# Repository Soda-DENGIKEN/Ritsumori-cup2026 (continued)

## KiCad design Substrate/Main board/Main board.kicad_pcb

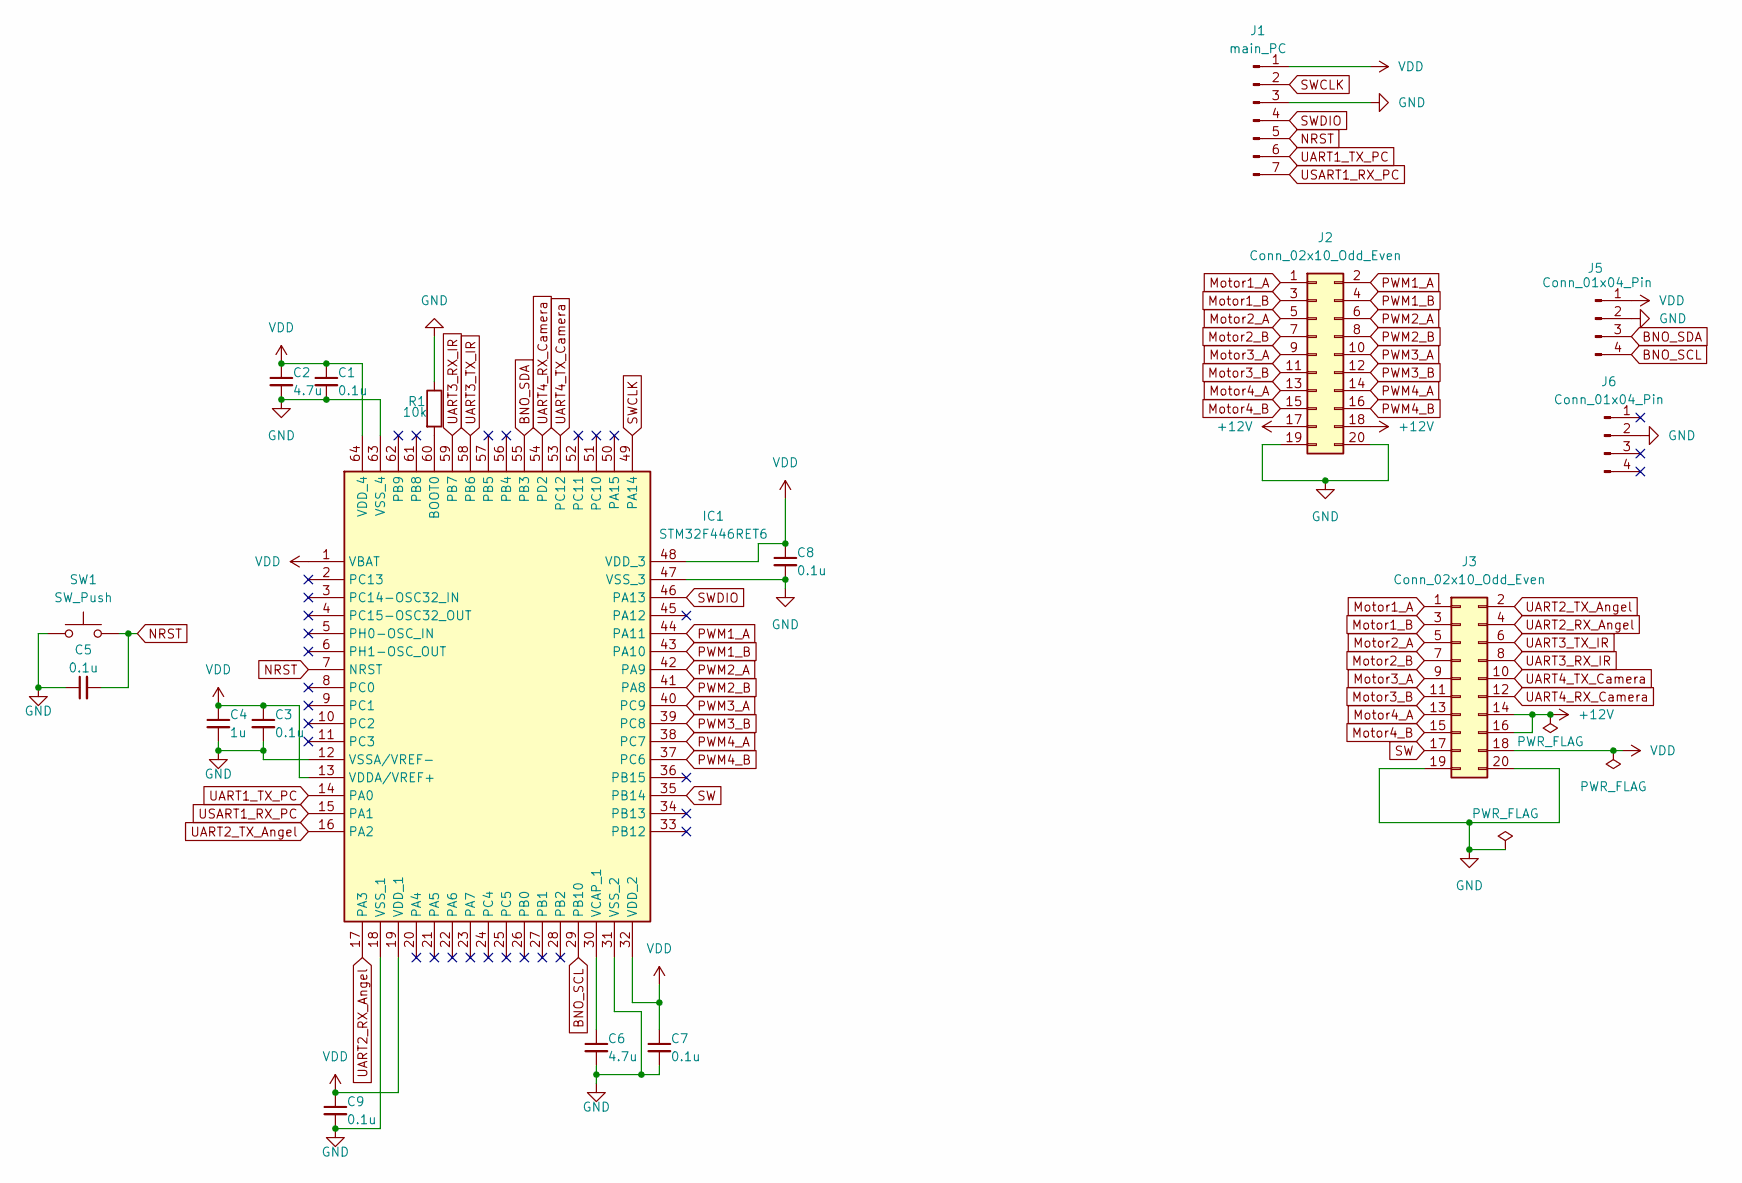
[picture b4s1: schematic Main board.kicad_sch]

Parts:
C1, C3, C5, C7, C8, C9: 0.1u; C_0603_1608Metric
C2, C6: 4.7u; C_0603_1608Metric
C4: 1u; C_0603_1608Metric
IC1: STM32F446RET6; LQFP-64_10x10mm_P0.5mm; Manufacturer_Part_Number STM32F446RET6; Mouser Part Number 511-STM32F446RET6
J1: main_PC; PinHeader_1x07_P2.54mm_Vertical
J2: Conn_02x10_Odd_Even; PinHeader_2x10_P2.54mm_Vertical
J3: Conn_02x10_Odd_Even; IDC-Header_2x10_P2.54mm_Vertical
J5, J6: Conn_01x04_Pin; PinSocket_1x04_P2.54mm_Vertical
R1: 10k; R_0603_1608Metric
SW1: SW_Push; SKRPABE010

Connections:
+12V: J2.17, J2.18, J3.14, J3.16
BNO_SCL: IC1.29 (PB10), J5.4
BNO_SDA: IC1.55 (PB3), J5.3
GND: C1.2, C2.2, C3.2, C4.2, C5.1, C6.2, C7.2, C8.2, C9.2, IC1.12 (VSSA/VREF-), IC1.18 (VSS_1), IC1.31 (VSS_2), IC1.47 (VSS_3), IC1.63 (VSS_4), J1.3, J2.19, J2.20, J3.19, J3.20, J5.2, J6.2, R1.1, SW1.1
Motor1_A: J2.1, J3.1
Motor1_B: J2.3, J3.3
Motor2_A: J2.5, J3.5
Motor2_B: J2.7, J3.7
Motor3_A: J2.9, J3.9
Motor3_B: J2.11, J3.11
Motor4_A: J2.13, J3.13
Motor4_B: J2.15, J3.15
NRST: C5.2, IC1.7 (NRST), J1.5, SW1.2
unnamed: IC1.60 (BOOT0), R1.2
unnamed: C6.1, IC1.30 (VCAP_1)
PWM1_A: IC1.44 (PA11), J2.2
PWM1_B: IC1.43 (PA10), J2.4
PWM2_A: IC1.42 (PA9), J2.6
PWM2_B: IC1.41 (PA8), J2.8
PWM3_A: IC1.40 (PC9), J2.10
PWM3_B: IC1.39 (PC8), J2.12
PWM4_A: IC1.38 (PC7), J2.14
PWM4_B: IC1.37 (PC6), J2.16
SW: IC1.35 (PB14), J3.17
SWCLK: IC1.49 (PA14), J1.2
SWDIO: IC1.46 (PA13), J1.4
UART1_TX_PC: IC1.14 (PA0), J1.6
UART2_RX_Angel: IC1.17 (PA3), J3.4
UART2_TX_Angel: IC1.16 (PA2), J3.2
UART3_RX_IR: IC1.59 (PB7), J3.8
UART3_TX_IR: IC1.58 (PB6), J3.6
UART4_RX_Camera: IC1.54 (PD2), J3.12
UART4_TX_Camera: IC1.53 (PC12), J3.10
USART1_RX_PC: IC1.15 (PA1), J1.7
VDD: C1.1, C2.1, C3.1, C4.1, C7.1, C8.1, C9.1, IC1.1 (VBAT), IC1.13 (VDDA/VREF+), IC1.19 (VDD_1), IC1.32 (VDD_2), IC1.48 (VDD_3), IC1.64 (VDD_4), J1.1, J3.18, J5.1

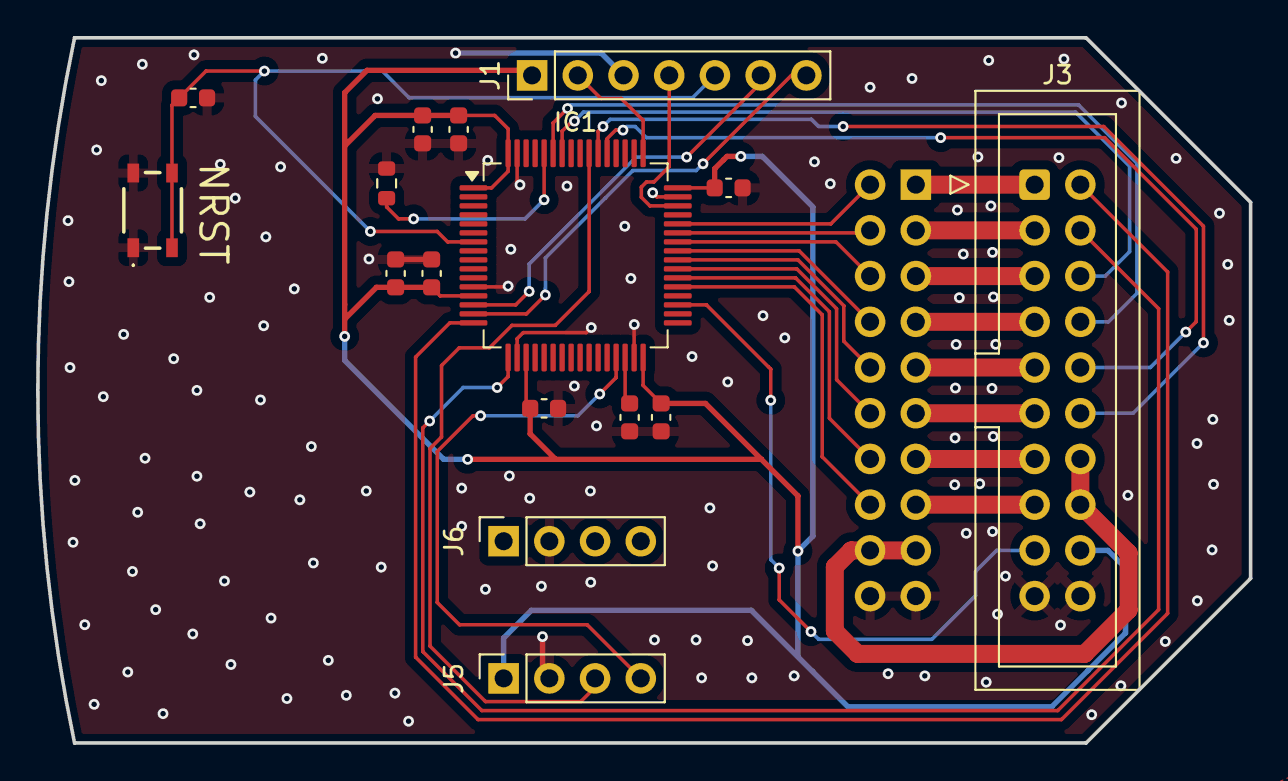
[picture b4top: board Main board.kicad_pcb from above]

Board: 2 copper layers, 67.4 x 39.2 mm, 17 parts (1 on the bottom side), 35 nets.

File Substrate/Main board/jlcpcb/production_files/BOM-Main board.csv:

Comment,Designator,Footprint,LCSC,Quantity
0.1u,"C1,C3,C5,C7,C8,C9",C_0603_1608Metric,C14663,6
10k,R1,R_0603_1608Metric,C25804,1
1u,C4,C_0603_1608Metric,C15849,1
4.7u,C2,C_0603_1608Metric,C19666,1
4.7u,C6,C_0603_1608Metric,C59461,1
STM32F446RET6,IC1,LQFP-64_10x10mm_P0.5mm,C69336,1
Conn_02x10_Odd_Even,J3,IDC-Header_2x10_P2.54mm_Vertical,,1
main_PC,J1,PinHeader_1x07_P2.54mm_Vertical,,1
SW_Push,SW1,SKRPABE010,,1
Conn_01x04_Pin,J6,PinSocket_1x04_P2.54mm_Vertical,,1
Conn_01x04_Pin,J5,PinSocket_1x04_P2.54mm_Vertical,,1
Conn_02x10_Odd_Even,J2,PinHeader_2x10_P2.54mm_Vertical,,1

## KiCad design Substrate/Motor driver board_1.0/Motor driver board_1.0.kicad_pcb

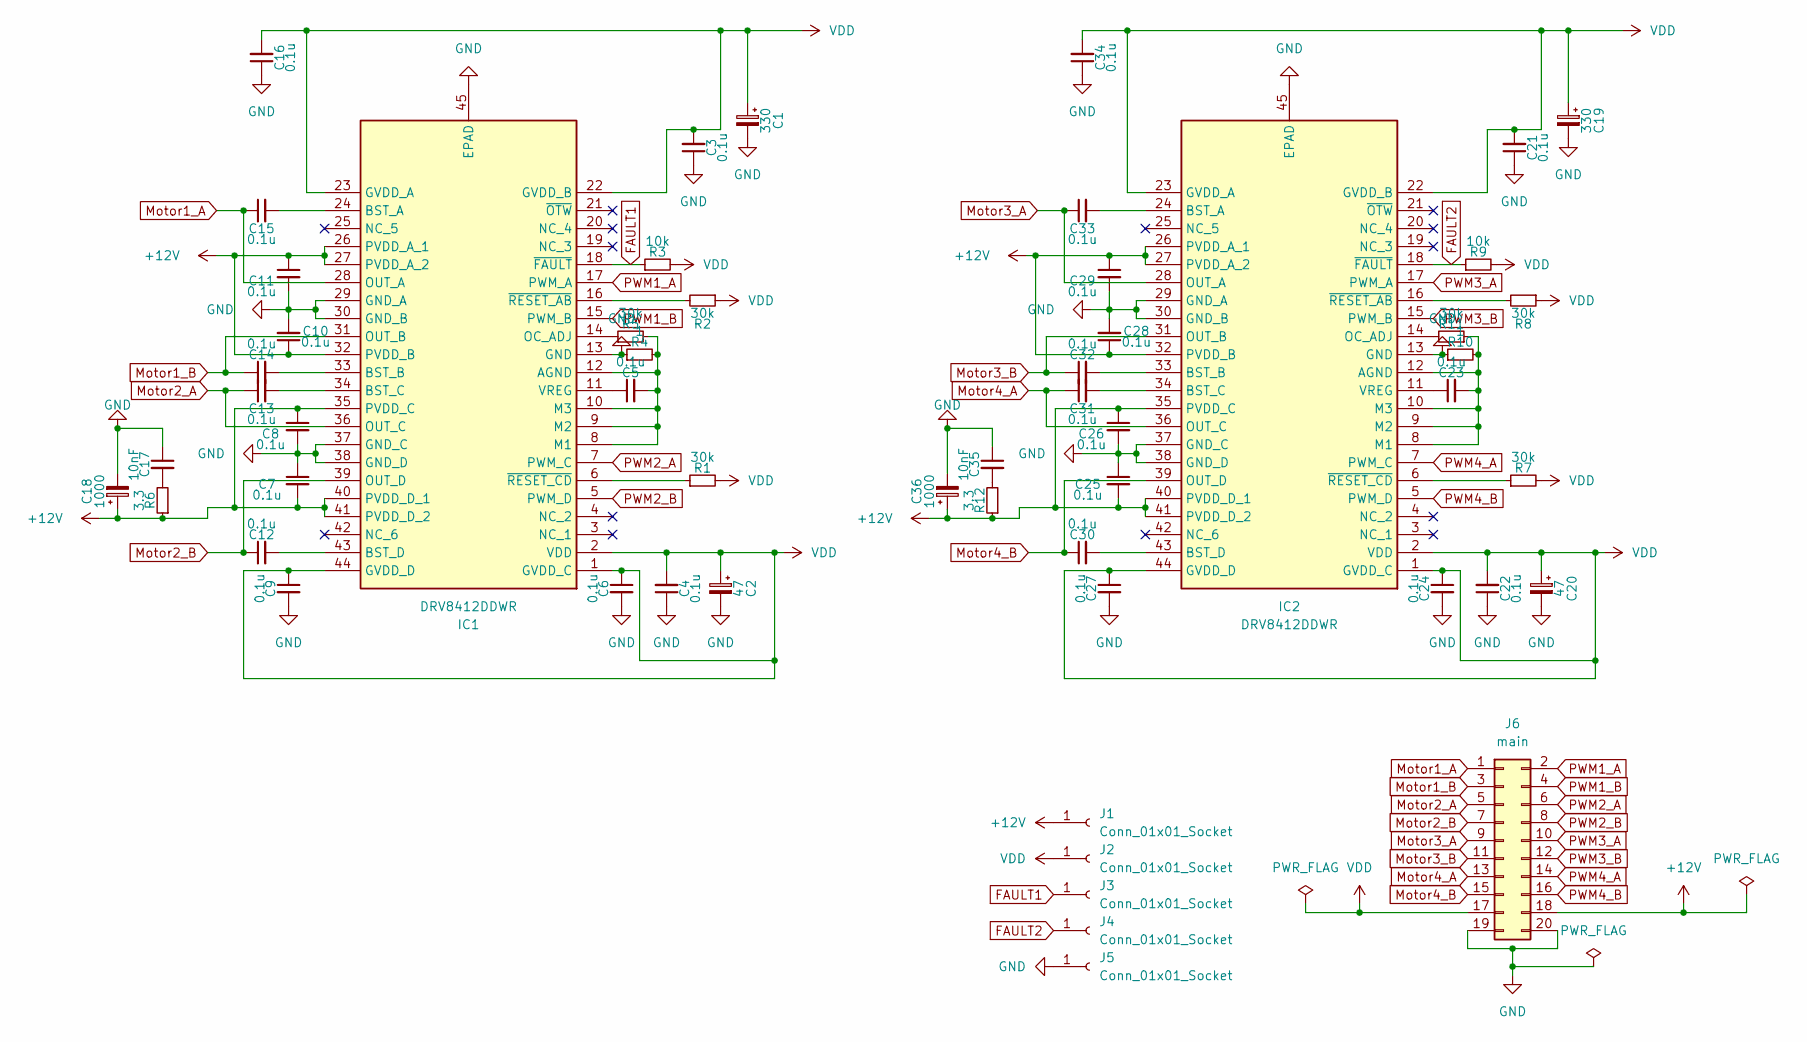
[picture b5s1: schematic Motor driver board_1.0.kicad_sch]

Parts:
C1, C19: 330; CP_Radial_D10.0mm_P5.00mm
C2, C20: 47; CP_Radial_D6.3mm_P2.50mm
C3, C4, C5, C6, C7, C8, C9, C10, C11, C12, C13, C14, C15, C16, C21, C22, C23, C24, C25, C26, C27, C28, C29, C30, C31, C32, C33, C34: 0.1u; C_0603_1608Metric
C17, C35: 10nF; C_0603_1608Metric
C18, C36: 1000; CP_Radial_D10.0mm_P5.00mm
IC1, IC2: DRV8412DDWR; HTSSOP-44-1EP_6.1x14mm_P0.635mm_EP5.2x14mm_Mask4.31x8.26mm; Manufacturer_Part_Number DRV8412DDWR
J1, J2, J3, J4, J5: Conn_01x01_Socket; TestPoint_Keystone_5000-5004_Miniature
J6: main; PinSocket_2x10_P2.54mm_Vertical
R1, R2, R5, R7, R8, R11: 30k; R_0603_1608Metric
R3, R9: 10k; R_0603_1608Metric
R4, R10: 1; R_0603_1608Metric
R6, R12: 3.3; R_0603_1608Metric

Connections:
+12V: C7.2, C8.1, C10.1, C11.1, C18.1, C25.2, C26.1, C28.1, C29.1, C36.1, IC1.26 (PVDD_A_1), IC1.27 (PVDD_A_2), IC1.32 (PVDD_B), IC1.35 (PVDD_C), IC1.40 (PVDD_D_1), IC1.41 (PVDD_D_2), IC2.26 (PVDD_A_1), IC2.27 (PVDD_A_2), IC2.32 (PVDD_B), IC2.35 (PVDD_C), IC2.40 (PVDD_D_1), IC2.41 (PVDD_D_2), J1.1, J6.18, R6.1, R12.1; also elsewhere on the board
FAULT1: IC1.18 (~FAULT), J3.1, R3.1; also elsewhere on the board
FAULT2: IC2.18 (~FAULT), J4.1, R9.1; also elsewhere on the board
GND: C1.2, C2.2, C3.1, C4.1, C6.2, C7.1, C8.2, C9.2, C10.2, C11.2, C16.1, C17.1, C18.2, C19.2, C20.2, C21.1, C22.1, C24.2, C25.1, C26.2, C27.2, C28.2, C29.2, C34.1, C35.1, C36.2, IC1.13 (GND), IC1.29 (GND_A), IC1.30 (GND_B), IC1.37 (GND_C), IC1.38 (GND_D), IC1.45 (EPAD), IC2.13 (GND), IC2.29 (GND_A), IC2.30 (GND_B), IC2.37 (GND_C), IC2.38 (GND_D), IC2.45 (EPAD), J5.1, J6.19, J6.20, R4.1, R10.1; also elsewhere on the board
Motor1_A: C15.1, IC1.28 (OUT_A), J6.1
Motor1_B: C14.1, IC1.31 (OUT_B), J6.3
Motor2_A: C13.1, IC1.36 (OUT_C), J6.5
Motor2_B: C12.1, IC1.39 (OUT_D), J6.7
Motor3_A: C33.1, IC2.28 (OUT_A), J6.9
Motor3_B: C32.1, IC2.31 (OUT_B), J6.11
Motor4_A: C31.1, IC2.36 (OUT_C), J6.13
Motor4_B: C30.1, IC2.39 (OUT_D), J6.15
unnamed: C17.2, R6.2
unnamed: C35.2, R12.2
unnamed: C5.2, IC1.8 (M1), IC1.9 (M2), IC1.10 (M3), IC1.12 (AGND), R4.2, R5.2
unnamed: C15.2, IC1.24 (BST_A)
unnamed: C14.2, IC1.33 (BST_B)
unnamed: C13.2, IC1.34 (BST_C)
unnamed: C12.2, IC1.43 (BST_D)
unnamed: IC1.14 (OC_ADJ), R5.1
unnamed: C5.1, IC1.11 (VREG)
unnamed: IC1.16 (~RESET_AB), R2.2
unnamed: IC1.6 (~RESET_CD), R1.1
unnamed: C23.2, IC2.8 (M1), IC2.9 (M2), IC2.10 (M3), IC2.12 (AGND), R10.2, R11.1
unnamed: C33.2, IC2.24 (BST_A)
unnamed: C32.2, IC2.33 (BST_B)
unnamed: C31.2, IC2.34 (BST_C)
unnamed: C30.2, IC2.43 (BST_D)
unnamed: IC2.14 (OC_ADJ), R11.2
unnamed: C23.1, IC2.11 (VREG)
unnamed: IC2.16 (~RESET_AB), R8.2
unnamed: IC2.6 (~RESET_CD), R7.1
PWM1_A: IC1.17 (PWM_A), J6.2
PWM1_B: IC1.15 (PWM_B), J6.4
PWM2_A: IC1.7 (PWM_C), J6.6
PWM2_B: IC1.5 (PWM_D), J6.8
PWM3_A: IC2.17 (PWM_A), J6.10
PWM3_B: IC2.15 (PWM_B), J6.12
PWM4_A: IC2.7 (PWM_C), J6.14
PWM4_B: IC2.5 (PWM_D), J6.16
VDD: C1.1, C2.1, C3.2, C4.2, C6.1, C9.1, C16.2, C19.1, C20.1, C21.2, C22.2, C24.1, C27.1, C34.2, IC1.1 (GVDD_C), IC1.2 (VDD), IC1.22 (GVDD_B), IC1.23 (GVDD_A), IC1.44 (GVDD_D), IC2.1 (GVDD_C), IC2.2 (VDD), IC2.22 (GVDD_B), IC2.23 (GVDD_A), IC2.44 (GVDD_D), J2.1, J6.17, R1.2, R2.1, R3.2, R7.2, R8.1, R9.2; also elsewhere on the board

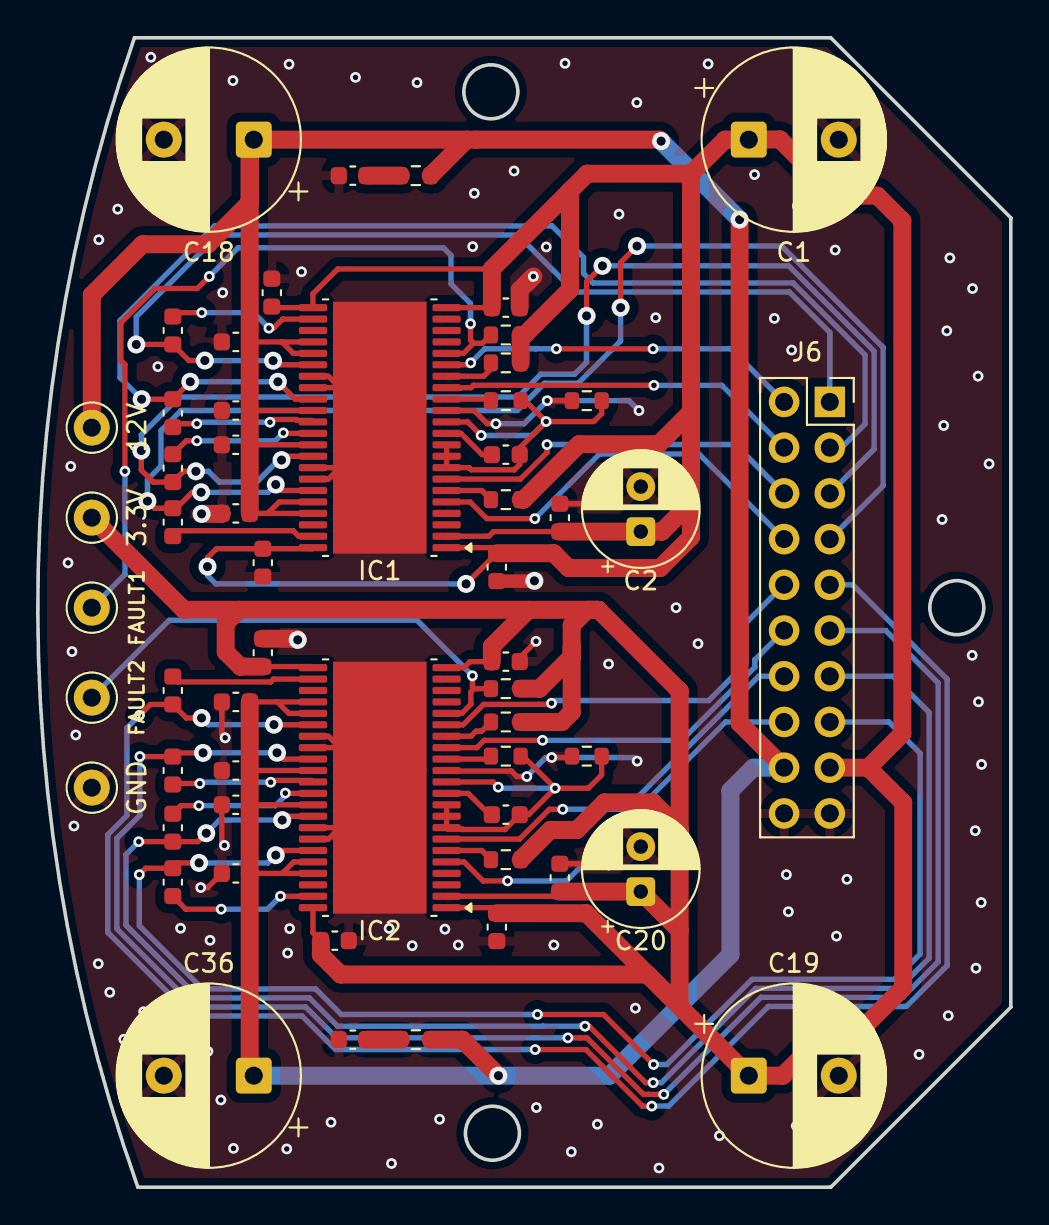
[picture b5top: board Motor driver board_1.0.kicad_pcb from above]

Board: 2 copper layers, 54.1 x 63.9 mm, 56 parts (0 on the bottom side), 41 nets.

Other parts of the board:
3.3V, 12V: Conn_01x01_Socket; TestPoint_Keystone_5000-5004_Miniature
FAULT1, FAULT2: Conn_01x01_Socket; TestPoint_Keystone_5000-5004_Miniature
GND: Conn_01x01_Socket; TestPoint_Keystone_5000-5004_Miniature

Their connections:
+12V: 12V.1; also elsewhere on the board
FAULT1: FAULT1.1; also elsewhere on the board
FAULT2: FAULT2.1; also elsewhere on the board
GND: GND.1; also elsewhere on the board
VDD: 3.3V.1; also elsewhere on the board

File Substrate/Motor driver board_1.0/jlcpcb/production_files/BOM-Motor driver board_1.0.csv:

Comment,Designator,Footprint,LCSC,Quantity
0.1u,"C10,C11,C12,C13,C14,C15,C16,C21,C22,C23,C24,C25,C26,C27,C28,C29,C3,C30,C31,C32,C33,C34,C4,C5,C6,C7,C8,C9",C_0603_1608Metric,C14663,28
1,"R10,R4",R_0603_1608Metric,C22936,2
10k,"R3,R9",R_0603_1608Metric,C25804,2
10nF,"C17,C35",C_0603_1608Metric,C57112,2
3.3,"R12,R6",R_0603_1608Metric,C22979,2
30k,"R1,R11,R2,R5,R7,R8",R_0603_1608Metric,C22984,6
DRV8412DDWR,"IC1,IC2",HTSSOP-44-1EP_6.1x14mm_P0.635mm_EP5.2x14mm_Mask4.31x8.26mm,C79852,2

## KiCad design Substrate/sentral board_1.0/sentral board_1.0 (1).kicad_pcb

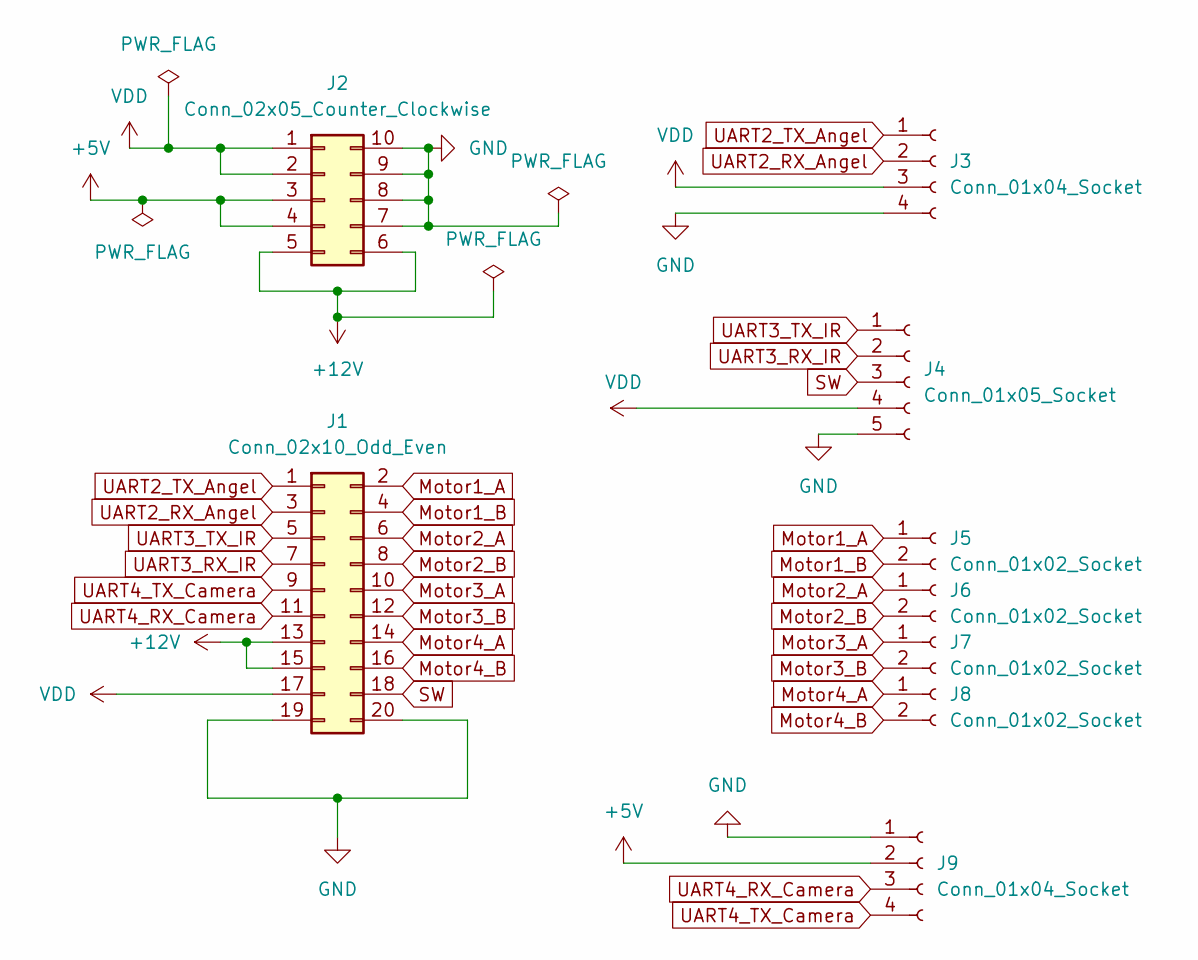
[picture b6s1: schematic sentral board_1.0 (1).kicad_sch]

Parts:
J1: Conn_02x10_Odd_Even; IDC-Header_2x10_P2.54mm_Vertical
J2: Conn_02x05_Counter_Clockwise; IDC-Header_2x05_P2.54mm_Vertical
J3, J9: Conn_01x04_Socket; JST_XH_B4B-XH-A_1x04_P2.50mm_Vertical
J4: Conn_01x05_Socket; JST_XH_B5B-XH-A_1x05_P2.50mm_Vertical
J5, J6, J7, J8: Conn_01x02_Socket; JST_XH_S2B-XH-A_1x02_P2.50mm_Horizontal

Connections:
+5V: J2.3, J2.4, J9.2
+12V: J1.13, J1.15, J2.5, J2.6
GND: J1.19, J1.20, J2.7, J2.8, J2.9, J2.10, J3.4, J4.5, J9.1
Motor1_A: J1.2, J5.1
Motor1_B: J1.4, J5.2
Motor2_A: J1.6, J6.1
Motor2_B: J1.8, J6.2
Motor3_A: J1.10, J7.1
Motor3_B: J1.12, J7.2
Motor4_A: J1.14, J8.1
Motor4_B: J1.16, J8.2
SW: J1.18, J4.3
UART2_RX_Angel: J1.3, J3.2
UART2_TX_Angel: J1.1, J3.1
UART3_RX_IR: J1.7, J4.2
UART3_TX_IR: J1.5, J4.1
UART4_RX_Camera: J1.11, J9.3
UART4_TX_Camera: J1.9, J9.4
VDD: J1.17, J2.1, J2.2, J3.3, J4.4

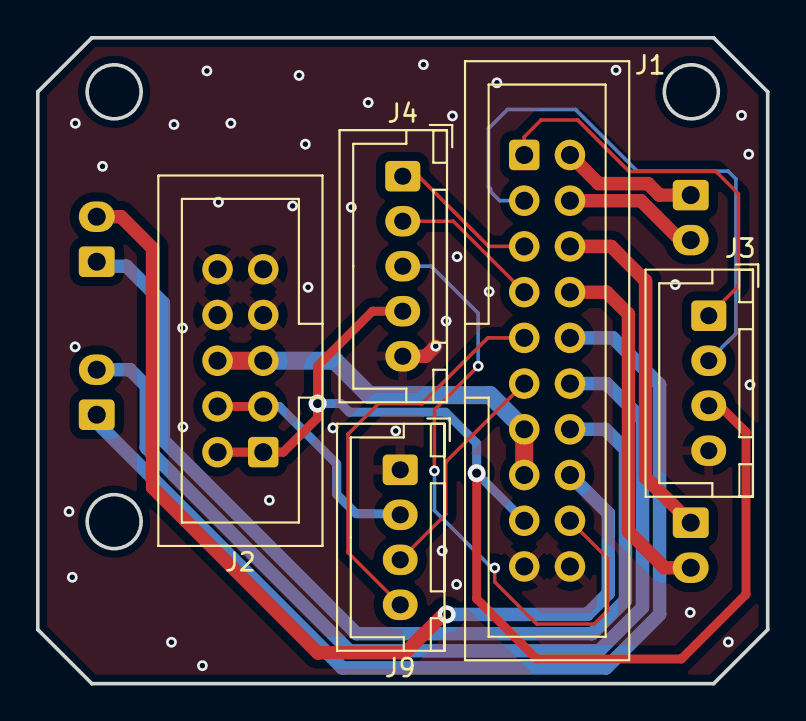
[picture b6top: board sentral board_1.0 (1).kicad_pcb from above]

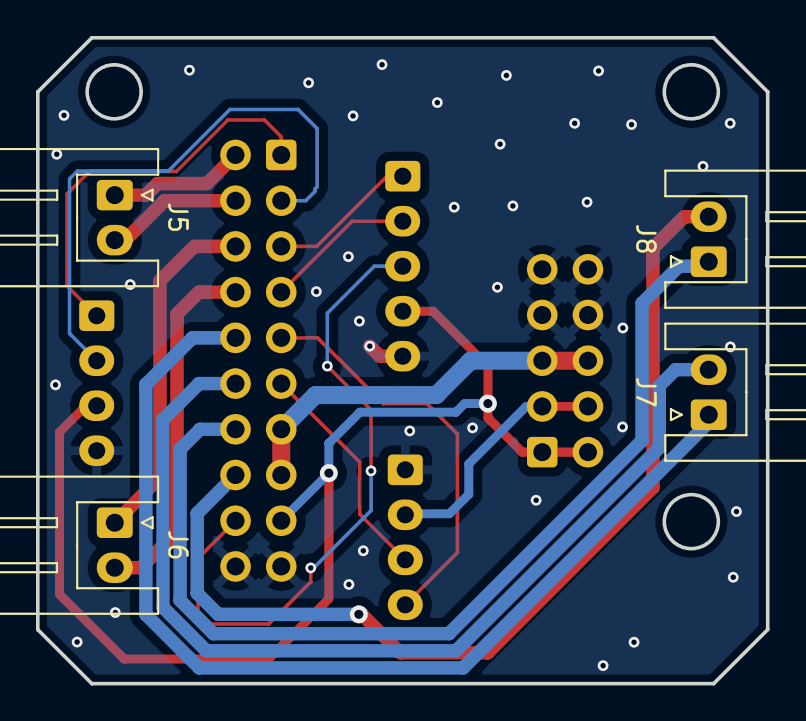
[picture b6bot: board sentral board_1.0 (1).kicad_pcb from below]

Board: 2 copper layers, 40.6 x 35.9 mm, 9 parts (4 on the bottom side), 19 nets.

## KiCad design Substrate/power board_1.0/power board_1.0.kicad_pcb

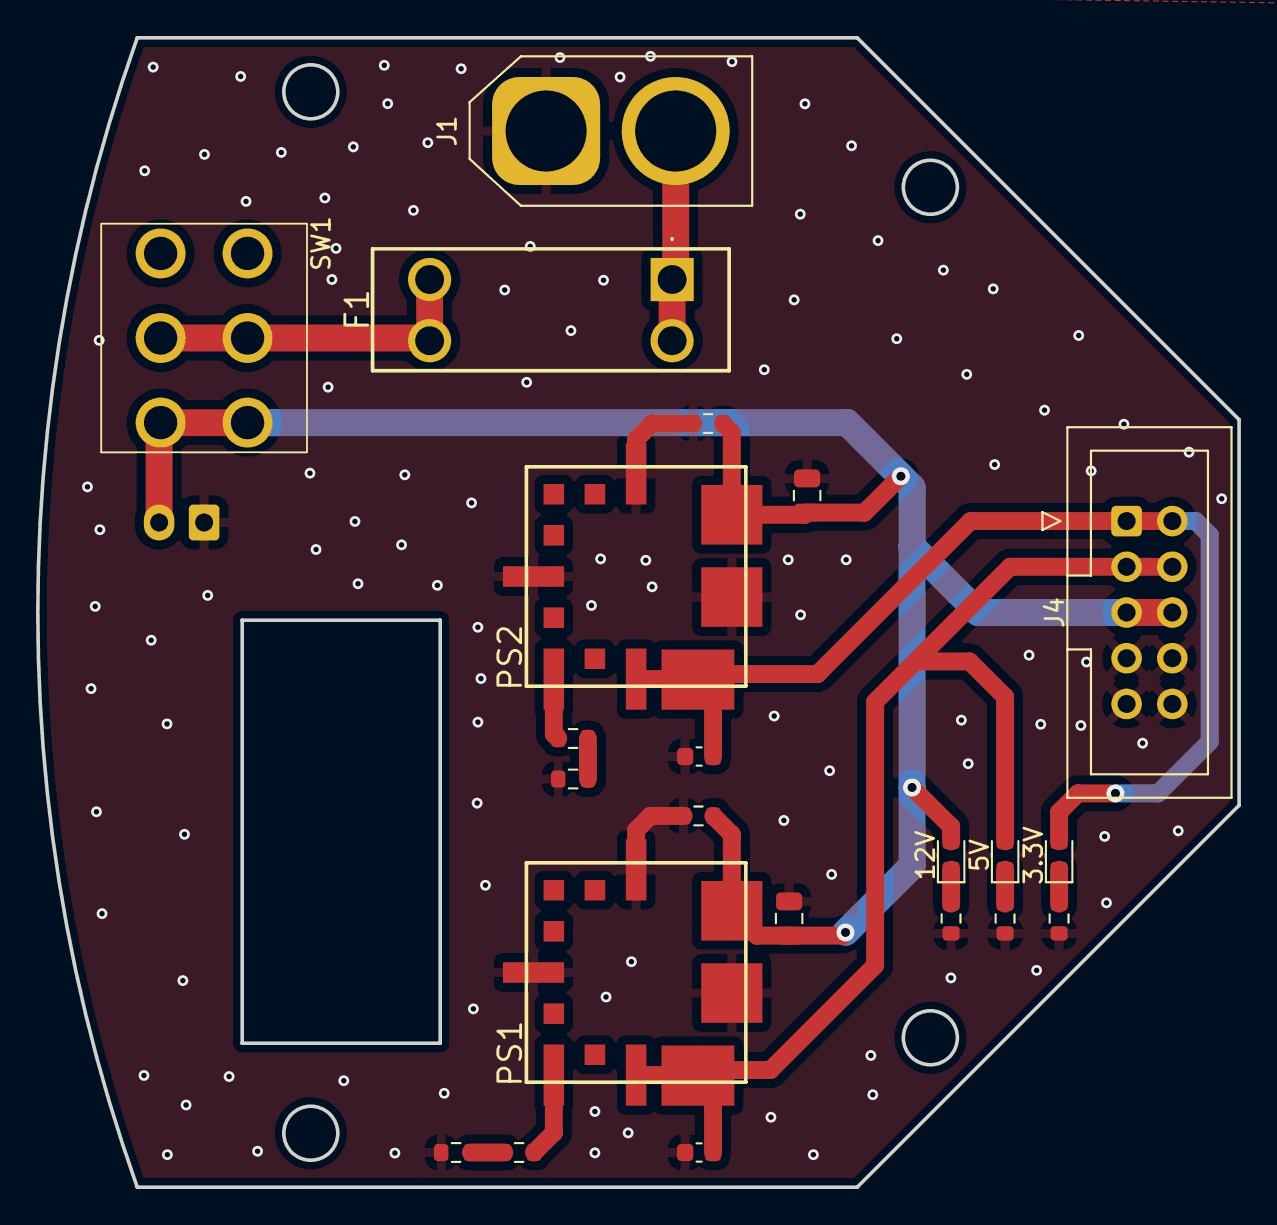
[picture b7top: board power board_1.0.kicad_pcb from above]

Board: 2 copper layers, 66.7 x 63.9 mm, 23 parts (1 on the bottom side), 13 nets.

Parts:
3.3V, 5V, 12V: LED; LED_0603_1608Metric
C1, C3: 22u; C_0805_2012Metric
C2, C4: 10u; C_0603_1608Metric
F1: Fuse; 355715
J1: Conn_01x02_Socket; AMASS_XT60-M_1x02_P7.20mm_Vertical
J2: 電圧計; JST_XH_B2B-XH-A_1x02_P2.50mm_Vertical
J4: Conn_02x05_Counter_Clockwise; IDC-Header_2x05_P2.54mm_Vertical
PS1, PS2: OKL-T_6-W12N-C; OKLT6W12NC
R1, R9: 680; R_0603_1608Metric
R2: 200; R_0603_1608Metric
R3: 75; R_0603_1608Metric
R4, R7: 20k; R_0603_1608Metric
R5: 1k; R_0603_1608Metric
R6: 330; R_0603_1608Metric
R8: 1.5k; R_0603_1608Metric
SW1: SW_Push_DPDT; Toggle

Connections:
+3.3V: 3.3V.2 (A), C4.1, J4.1, J4.2, PS2.4 (VOUT), PS2.5 (SENSE)
+5V: 5V.2 (A), C2.1, J4.3, J4.4, PS1.4 (VOUT), PS1.5 (SENSE)
+12V: 12V.2 (A), C1.1, C3.1, J2.2, J4.5, J4.6, PS1.2 (VIN), PS2.2 (VIN), R4.1, R7.1, SW1.1 (A), SW1.4 (A)
GND: C1.2, C2.2, C3.2, C4.2, J1.1, J2.1, J4.7, J4.8, J4.9, J4.10, PS1.1 (ON/OFF_CONTROL), PS1.3 (GROUND_1), PS1.7 (GROUND_2), PS2.1 (ON/OFF_CONTROL), PS2.3 (GROUND_1), PS2.7 (GROUND_2), R1.1, R2.1, R3.1, R4.2, R6.2, R7.2, R9.2
unnamed: 12V.1 (K), R1.2
unnamed: 5V.1 (K), R2.2
unnamed: 3.3V.1 (K), R3.2
unnamed: F1.2, SW1.2 (B), SW1.5 (B)
unnamed: F1.1, J1.2
unnamed: PS1.6 (TRIM), R5.1
unnamed: PS2.6 (TRIM), R8.1
unnamed: R5.2, R6.1
unnamed: R8.2, R9.1

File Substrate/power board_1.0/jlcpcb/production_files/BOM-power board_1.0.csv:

Comment,Designator,Footprint,LCSC,Quantity
1.5k,R8,R_0603_1608Metric,C22843,1
10u,"C2,C4",C_0603_1608Metric,C96446,2
1k,R5,R_0603_1608Metric,C21190,1
200,R2,R_0603_1608Metric,C8218,1
20k,"R4,R7",R_0603_1608Metric,C4184,2
22u,"C1,C3",C_0805_2012Metric,C45783,2
330,R6,R_0603_1608Metric,C23138,1
680,"R1,R9",R_0603_1608Metric,C23228,2
75,R3,R_0603_1608Metric,C4275,1
LED,"12V,3.3V,5V",LED_0603_1608Metric,C2286,3
OKL-T_6-W12N-C,PS2,OKLT6W12NC,,1
Fuse,F1,355715,,1
SW_Push_DPDT,SW1,Toggle,,1
Conn_01x02_Socket,J1,AMASS_XT60-M_1x02_P7.20mm_Vertical,,1
Conn_02x05_Counter_Clockwise,J4,IDC-Header_2x05_P2.54mm_Vertical,,1
電圧計,J2,JST_XH_B2B-XH-A_1x02_P2.50mm_Vertical,,1
OKL-T_6-W12N-C,PS1,OKLT6W12NC,,1

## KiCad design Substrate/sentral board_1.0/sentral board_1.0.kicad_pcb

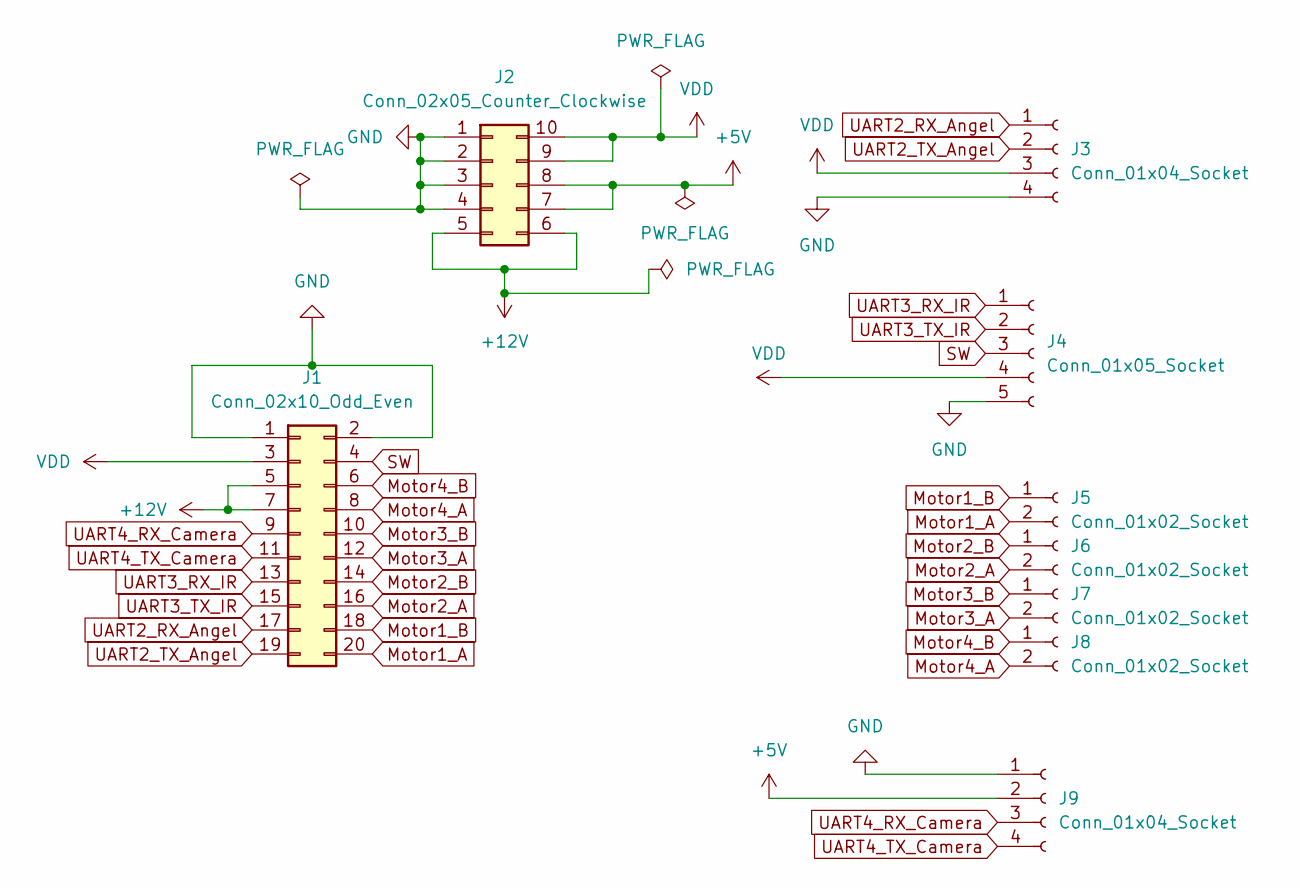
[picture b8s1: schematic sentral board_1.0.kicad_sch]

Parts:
J1: Conn_02x10_Odd_Even; IDC-Header_2x10_P2.54mm_Vertical
J2: Conn_02x05_Counter_Clockwise; IDC-Header_2x05_P2.54mm_Vertical
J3, J9: Conn_01x04_Socket; JST_XH_B4B-XH-A_1x04_P2.50mm_Vertical
J4: Conn_01x05_Socket; JST_XH_B5B-XH-A_1x05_P2.50mm_Vertical
J5, J6, J7, J8: Conn_01x02_Socket; JST_XH_S2B-XH-A_1x02_P2.50mm_Horizontal

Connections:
+5V: J2.7, J2.8, J9.2
+12V: J1.5, J1.7, J2.5, J2.6
GND: J1.1, J1.2, J2.1, J2.2, J2.3, J2.4, J3.4, J4.5, J9.1
Motor1_A: J1.20, J5.2
Motor1_B: J1.18, J5.1
Motor2_A: J1.16, J6.2
Motor2_B: J1.14, J6.1
Motor3_A: J1.12, J7.2
Motor3_B: J1.10, J7.1
Motor4_A: J1.8, J8.2
Motor4_B: J1.6, J8.1
SW: J1.4, J4.3
UART2_RX_Angel: J1.17, J3.1
UART2_TX_Angel: J1.19, J3.2
UART3_RX_IR: J1.13, J4.1
UART3_TX_IR: J1.15, J4.2
UART4_RX_Camera: J1.9, J9.3
UART4_TX_Camera: J1.11, J9.4
VDD: J1.3, J2.9, J2.10, J3.3, J4.4

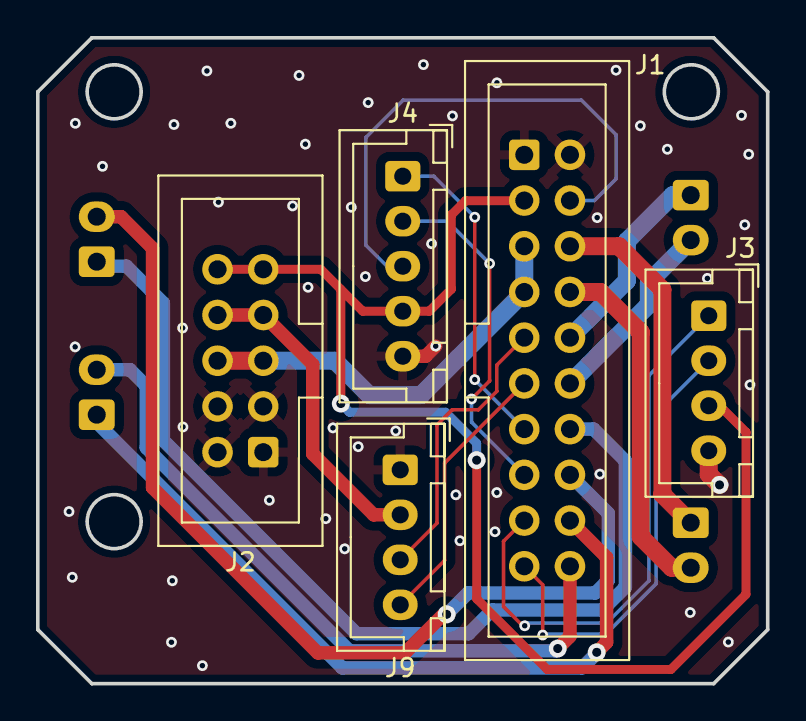
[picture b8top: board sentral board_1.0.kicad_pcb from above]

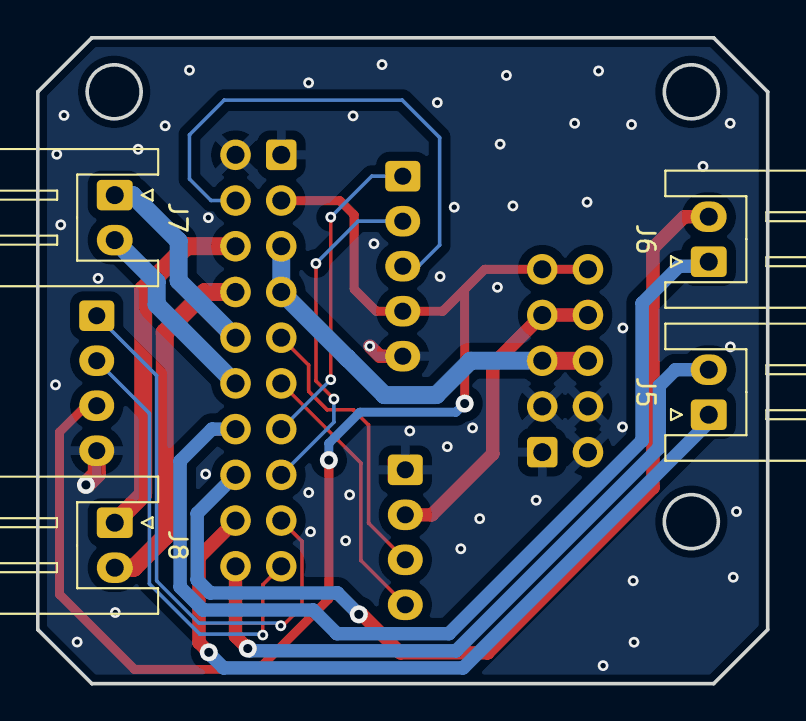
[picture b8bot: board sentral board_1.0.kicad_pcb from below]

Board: 2 copper layers, 40.6 x 35.9 mm, 9 parts (4 on the bottom side), 19 nets.

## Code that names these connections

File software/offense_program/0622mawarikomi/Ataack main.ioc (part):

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Mcu.Name=STM32F446R(C-E)Tx
Mcu.Package=LQFP64
Mcu.UserName=STM32F446RETx
PA0-WKUP.Mode=Asynchronous
PA0-WKUP.Signal=UART4_TX
PA1.Mode=Asynchronous
PA1.Signal=UART4_RX
PA10.Signal=S_TIM1_CH3
PA11.Signal=S_TIM1_CH4
PA2.Mode=Asynchronous
PA2.Signal=USART2_TX
PA3.Mode=Asynchronous
PA3.Signal=USART2_RX
PA8.Signal=S_TIM1_CH1
PA9.Signal=S_TIM1_CH2
PB10.Mode=I2C
PB10.Signal=I2C2_SCL
PB14.GPIOParameters=GPIO_Label
PB14.GPIO_Label=SW1
PB14.Signal=GPIO_Input
PB3.Mode=I2C
PB3.Signal=I2C2_SDA
PB6.Mode=Asynchronous
PB6.Signal=USART1_TX
PB7.Mode=Asynchronous
PB7.Signal=USART1_RX
PC12.Mode=Asynchronous
PC12.Signal=UART5_TX
PC6.Signal=S_TIM8_CH1
PC7.Signal=S_TIM8_CH2
PC8.Signal=S_TIM8_CH3
PC9.Signal=S_TIM8_CH4
PD2.Mode=Asynchronous
PD2.Signal=UART5_RX
RCC.SYSCLKFreq_VALUE=180000000
RCC.SYSCLKSource=RCC_SYSCLKSOURCE_PLLCLK
board=custom

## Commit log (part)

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2026-04-30 Auto Backup: 2026/04/30 16:20:54.74
2026-04-30 Auto Backup: 2026/04/30 17:59:40.97
2026-05-01 Auto Backup: 2026/05/01 15:16:02.62
2026-05-01 Auto Backup: 2026/05/01 21:29:52.15
2026-05-09 Auto Backup: 2026/05/09 13:41:35.03
2026-05-09 Auto Backup: 2026/05/09 18:25:44.11
2026-05-11 Auto Backup: 2026/05/11 16:03:42.80
2026-05-26 Auto Backup: 2026/05/26 21:11:23.16
2026-05-31 Auto Backup: 2026/05/31 18:11:55.32
2026-06-02 Auto Backup: 2026/06/02 17:05:48.36
2026-06-02 Auto Backup: 2026/06/02 21:53:49.02
2026-06-03 Auto Backup: 2026/06/03 19:18:46.00
2026-06-04 Auto Backup: 2026/06/04 20:32:27.09
2026-06-07 Auto Backup: 2026/06/07 21:51:40.26
2026-06-11 Auto Backup: 2026/06/11 21:55:46.39
2026-06-13 Auto Backup: 2026/06/13 16:04:30.94
2026-06-14 Auto Backup: 2026/06/14 21:59:11.65
2026-06-15 Auto Backup: 2026/06/15 20:57:05.64
2026-06-15 Auto Backup: 2026/06/15 21:55:05.64
2026-06-17 Auto Backup: 2026/06/17 21:13:14.64
2026-06-20 Auto Backup: 2026/06/21 1:51:04.38
